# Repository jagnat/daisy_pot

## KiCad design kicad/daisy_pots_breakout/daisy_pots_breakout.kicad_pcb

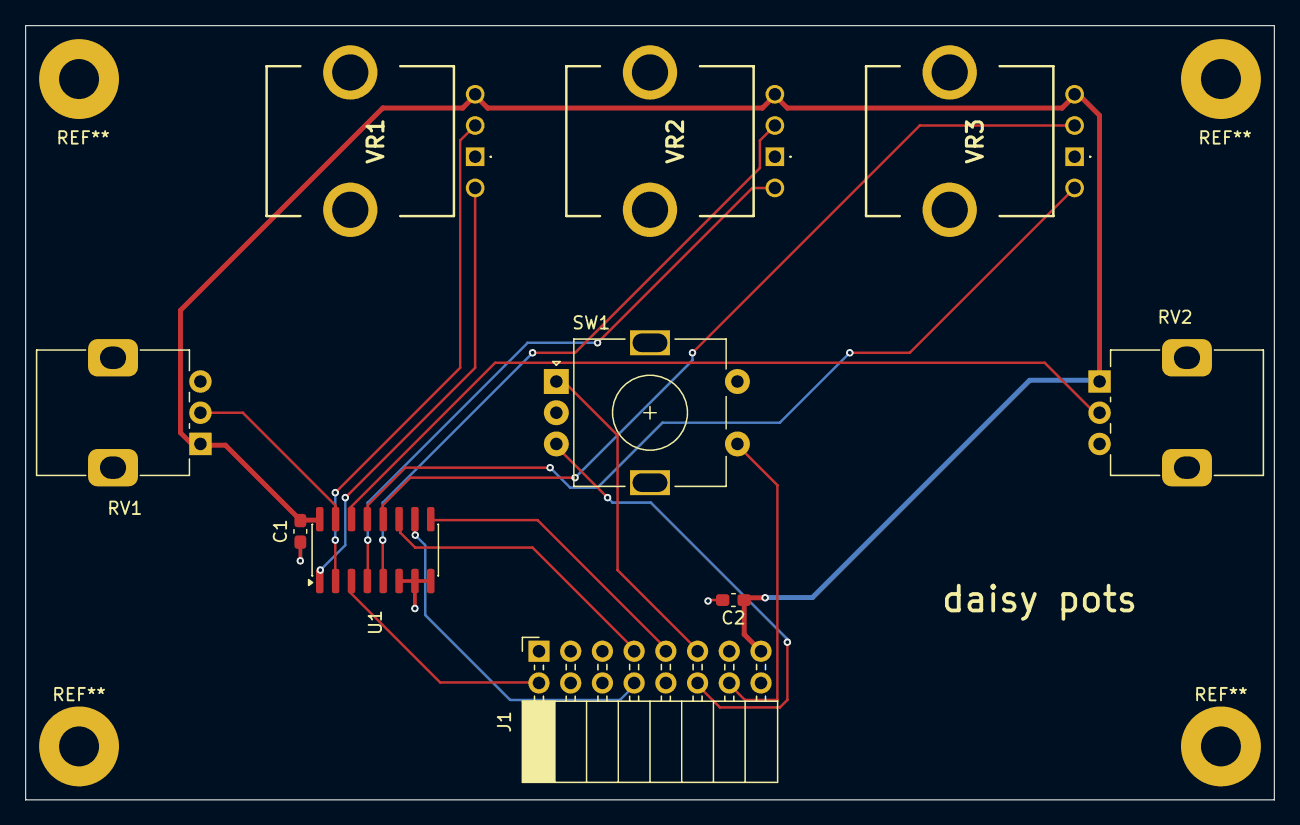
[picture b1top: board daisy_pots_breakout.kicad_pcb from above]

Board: 2 copper layers, 100.0 x 62.0 mm, 10 parts (0 on the bottom side), 17 nets.

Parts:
C1: 100nF; C_0603_1608Metric_Pad1.08x0.95mm_HandSolder
C2: 10uF; C_0603_1608Metric_Pad1.08x0.95mm_HandSolder
J1: Petal_2x08; PinSocket_2x08_P2.54mm_Horizontal
RV1, RV2: 10k; Potentiometer_Alps_RK09K_Single_Vertical
SW1: EC11E; RotaryEncoder_Alps_EC11E-Switch_Vertical_H20mm
U1: 74HC4051D; SOIC-16_3.9x9.9mm_P1.27mm
VR1, VR2, VR3: RV112FF-40B1; RV112FF40B115F0B20K0068

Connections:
+3.3VA: C1.1, C2.1, J1.15, RV1.1, RV2.1, U1.16, VR1.3 (CW), VR2.3 (CW), VR3.3 (CW)
/ADC: J1.2, U1.3
/A_S0: J1.7, U1.11
/A_S1: J1.8, U1.10
/A_S2: J1.9, U1.9
/ENC_A: J1.11, SW1.A
/ENC_B: J1.12, SW1.B
/ENC_SW: J1.14, SW1.S1
/JOY1_X: U1.2, VR1.2 (WIPER1)
/JOY1_Y: U1.1, VR1.A2 (WIPER2)
/JOY2_X: U1.5, VR2.2 (WIPER1)
/JOY2_Y: U1.4, VR2.A2 (WIPER2)
/JOY3_X: U1.12, VR3.2 (WIPER1)
/JOY3_Y: U1.13, VR3.A2 (WIPER2)
/POT1: RV1.2, U1.15
/POT2: RV2.2, U1.14
GND: C1.2, C2.2, J1.1, J1.3, J1.13, J1.16, RV1.3, RV2.3, SW1.C, SW1.S2, U1.6, U1.7, U1.8, VR1.1 (CCW), VR2.1 (CCW), VR3.1 (CCW)

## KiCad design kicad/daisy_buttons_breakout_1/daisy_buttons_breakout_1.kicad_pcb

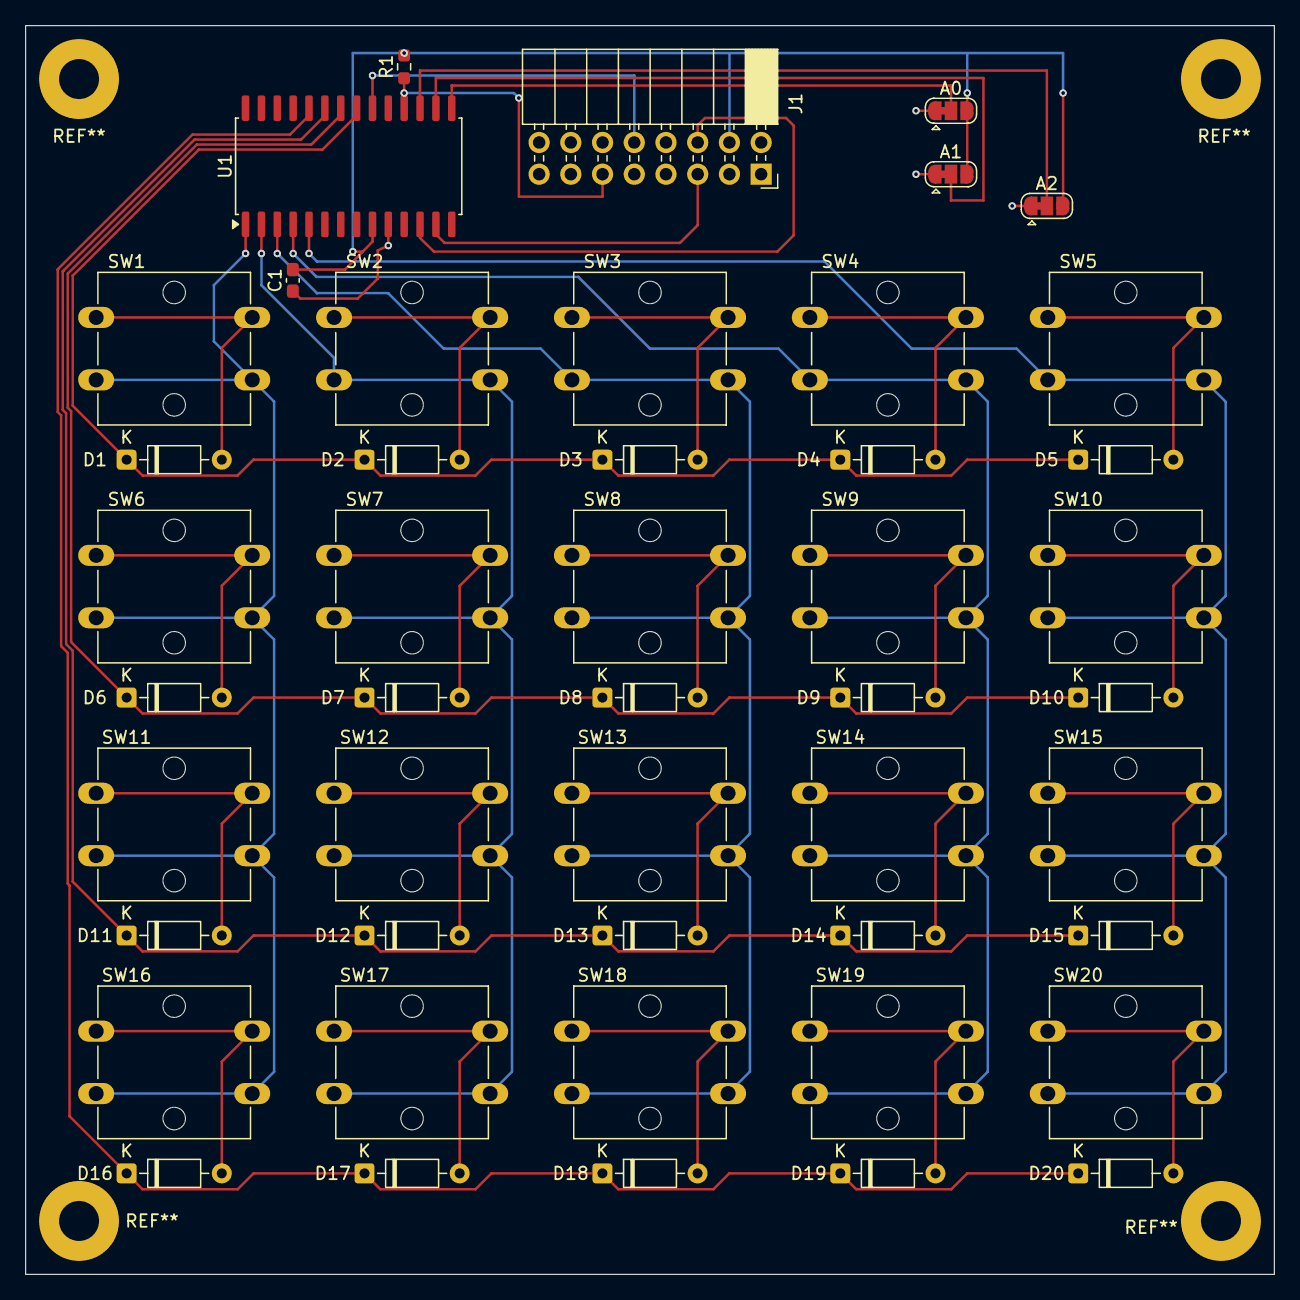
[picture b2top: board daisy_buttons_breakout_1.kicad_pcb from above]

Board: 2 copper layers, 100.0 x 100.0 mm, 47 parts (0 on the bottom side), 38 nets.

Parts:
A0, A1, A2: SolderJumper_3_Bridged12; SolderJumper-3_P1.3mm_Bridged12_RoundedPad1.0x1.5mm
C1: 100nF; C_0603_1608Metric_Pad1.08x0.95mm_HandSolder
D1, D2, D3, D4, D5, D6, D7, D8, D9, D10, D11, D12, D13, D14, D15, D16, D17, D18, D19, D20: D; D_DO-35_SOD27_P7.62mm_Horizontal
J1: Conn_02x08_Odd_Even; PinSocket_2x08_P2.54mm_Horizontal
R1: 10k; R_0603_1608Metric_Pad0.98x0.95mm_HandSolder
SW1, SW2, SW3, SW4, SW5, SW6, SW7, SW8, SW9, SW10, SW11, SW12, SW13, SW14, SW15, SW16, SW17, SW18, SW19, SW20: SW_Push; SW_SPST_Omron_B3F-50xx
U1: MCP23017x-x-SO; SOIC-28W_7.5x17.9mm_P1.27mm

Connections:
/A0: D1.1 (K), D2.1 (K), D3.1 (K), D4.1 (K), D5.1 (K), U1.21 (GPA0)
/A1: D6.1 (K), D7.1 (K), D8.1 (K), D9.1 (K), D10.1 (K), U1.22 (GPA1)
/A2: D11.1 (K), D12.1 (K), D13.1 (K), D14.1 (K), D15.1 (K), U1.23 (GPA2)
/A3: D16.1 (K), D17.1 (K), D18.1 (K), D19.1 (K), D20.1 (K), U1.24 (GPA3)
/B0: SW1.2, SW6.2, SW11.2, SW16.2, U1.1 (GPB0)
/B1: SW2.2, SW7.2, SW12.2, SW17.2, U1.2 (GPB1)
/B2: SW3.2, SW8.2, SW13.2, SW18.2, U1.3 (GPB2)
/B3: SW4.2, SW9.2, SW14.2, SW19.2, U1.4 (GPB3)
/B4: SW5.2, SW10.2, SW15.2, SW20.2, U1.5 (GPB4)
/INT_A: J1.10, U1.20 (INTA)
/RST: J1.11, R1.1, U1.18 (~RESET)
/SCK: J1.6, U1.12 (SCK)
/SDA: J1.5, U1.13 (SDA)
GND: A0.1 (A), A1.1 (A), A2.1 (A), C1.1, J1.1, J1.3, J1.13, J1.16, U1.10 (V_{SS})
unnamed: A0.2 (C), U1.15 (A0)
unnamed: A1.2 (C), U1.16 (A1)
unnamed: A2.2 (C), U1.17 (A2)
unnamed: D1.2 (A), SW1.1
unnamed: D2.2 (A), SW2.1
unnamed: D3.2 (A), SW3.1
unnamed: D4.2 (A), SW4.1
unnamed: D5.2 (A), SW5.1
unnamed: D6.2 (A), SW6.1
unnamed: D7.2 (A), SW7.1
unnamed: D8.2 (A), SW8.1
unnamed: D9.2 (A), SW9.1
unnamed: D10.2 (A), SW10.1
unnamed: D11.2 (A), SW11.1
unnamed: D12.2 (A), SW12.1
unnamed: D13.2 (A), SW13.1
unnamed: D14.2 (A), SW14.1
unnamed: D15.2 (A), SW15.1
unnamed: D16.2 (A), SW16.1
unnamed: D17.2 (A), SW17.1
unnamed: D18.2 (A), SW18.1
unnamed: D19.2 (A), SW19.1
unnamed: D20.2 (A), SW20.1
VCC: A0.3 (B), A1.3 (B), A2.3 (B), C1.2, J1.4, R1.2, U1.9 (V_{DD})

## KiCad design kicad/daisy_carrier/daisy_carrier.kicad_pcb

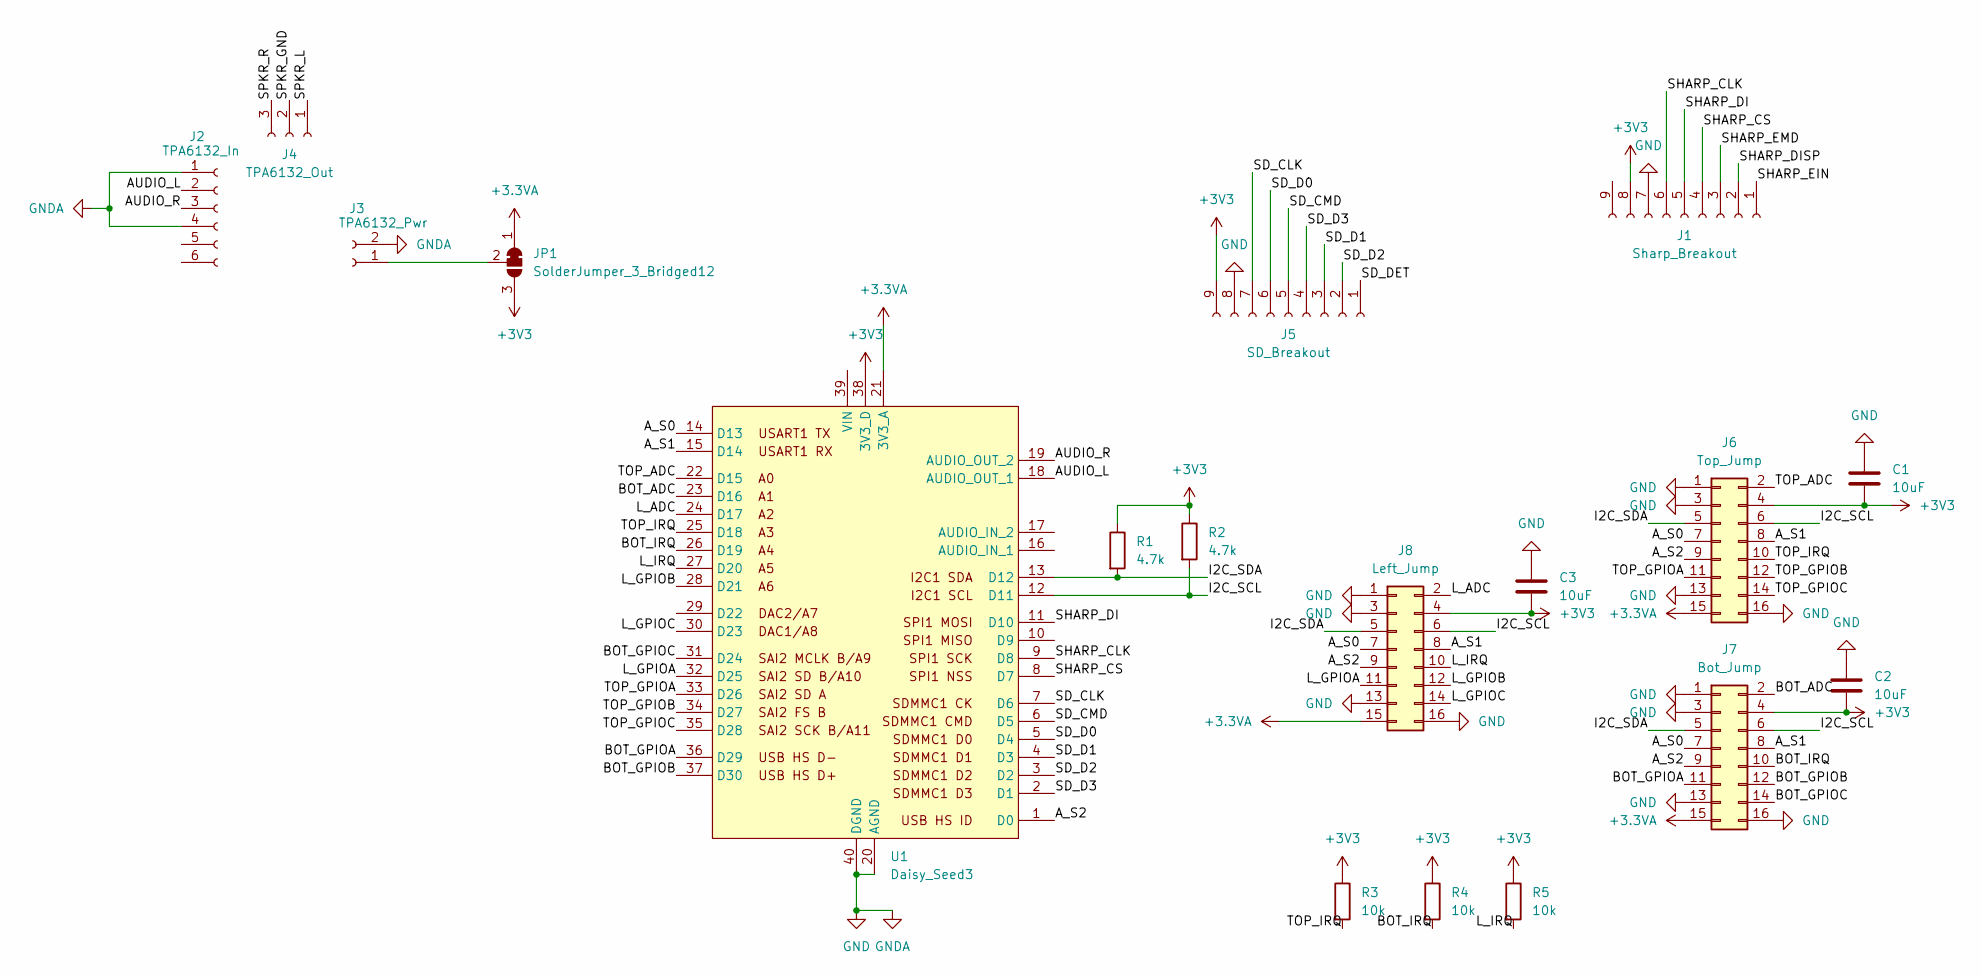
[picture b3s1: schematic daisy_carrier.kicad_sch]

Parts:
C1, C2, C3: 10uF; C_0603_1608Metric_Pad1.08x0.95mm_HandSolder
J1: Sharp_Breakout; PinSocket_1x09_P2.54mm_Vertical
J2: TPA6132_In; PinSocket_1x06_P2.54mm_Vertical
J3: TPA6132_Pwr; PinSocket_1x02_P2.54mm_Vertical
J4: TPA6132_Out; PinSocket_1x03_P2.54mm_Vertical
J5: SD_Breakout; PinSocket_1x09_P2.54mm_Vertical
J6: Top_Jump; PinHeader_2x08_P2.54mm_Horizontal
J7: Bot_Jump; PinHeader_2x08_P2.54mm_Horizontal
J8: Left_Jump; PinHeader_2x08_P2.54mm_Horizontal
JP1: SolderJumper_3_Bridged12; SolderJumper-3_P1.3mm_Bridged12_Pad1.0x1.5mm_NumberLabels
R1, R2: 4.7k; R_0603_1608Metric_Pad0.98x0.95mm_HandSolder
R3, R4, R5: 10k; R_0603_1608Metric_Pad0.98x0.95mm_HandSolder
U1: Daisy_Seed3; DAISY_SEED

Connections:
+3.3VA: J6.15, J7.15, J8.15, JP1.1 (A), U1.21 (3V3_A)
+3V3: C1.2, C2.2, C3.2, J1.8, J5.9, J6.4, J7.4, J8.4, JP1.3 (B), R1.1, R2.1, R3.1, R4.1, R5.1, U1.38 (3V3_D)
/AUDIO_L: J2.2, U1.18 (AUDIO_OUT_1)
/AUDIO_R: J2.3, U1.19 (AUDIO_OUT_2)
/A_S0: J6.7, J7.7, J8.7, U1.14 (D13)
/A_S1: J6.8, J7.8, J8.8, U1.15 (D14)
/A_S2: J6.9, J7.9, J8.9, U1.1 (D0)
/BOT_ADC: J7.2, U1.23 (D16)
/BOT_GPIOA: J7.11, U1.36 (D29)
/BOT_GPIOB: J7.12, U1.37 (D30)
/BOT_GPIOC: J7.14, U1.31 (D24)
/BOT_IRQ: J7.10, R4.2, U1.26 (D19)
/I2C_SCL: J6.6, J7.6, J8.6, R2.2, U1.12 (D11)
/I2C_SDA: J6.5, J7.5, J8.5, R1.2, U1.13 (D12)
/L_ADC: J8.2, U1.24 (D17)
/L_GPIOA: J8.11, U1.32 (D25)
/L_GPIOB: J8.12, U1.28 (D21)
/L_GPIOC: J8.14, U1.30 (D23)
/L_IRQ: J8.10, R5.2, U1.27 (D20)
/SD_CLK: J5.7, U1.7 (D6)
/SD_CMD: J5.5, U1.6 (D5)
/SD_D0: J5.6, U1.5 (D4)
/SD_D1: J5.3, U1.4 (D3)
/SD_D2: J5.2, U1.3 (D2)
/SD_D3: J5.4, U1.2 (D1)
/SD_DET: J5.1
/SHARP_CLK: J1.6, U1.9 (D8)
/SHARP_CS: J1.4, U1.8 (D7)
/SHARP_DI: J1.5, U1.11 (D10)
/SHARP_DISP: J1.2
/SHARP_EIN: J1.1
/SHARP_EMD: J1.3
/SPKR_GND: J4.2
/SPKR_L: J4.1
/SPKR_R: J4.3
/TOP_ADC: J6.2, U1.22 (D15)
/TOP_GPIOA: J6.11, U1.33 (D26)
/TOP_GPIOB: J6.12, U1.34 (D27)
/TOP_GPIOC: J6.14, U1.35 (D28)
/TOP_IRQ: J6.10, R3.2, U1.25 (D18)
GND: C1.1, C2.1, C3.1, J1.7, J2.1, J2.4, J3.2, J5.8, J6.1, J6.3, J6.13, J6.16, J7.1, J7.3, J7.13, J7.16, J8.1, J8.3, J8.13, J8.16, U1.20 (AGND), U1.40 (DGND)
unnamed: J3.1, JP1.2 (C)

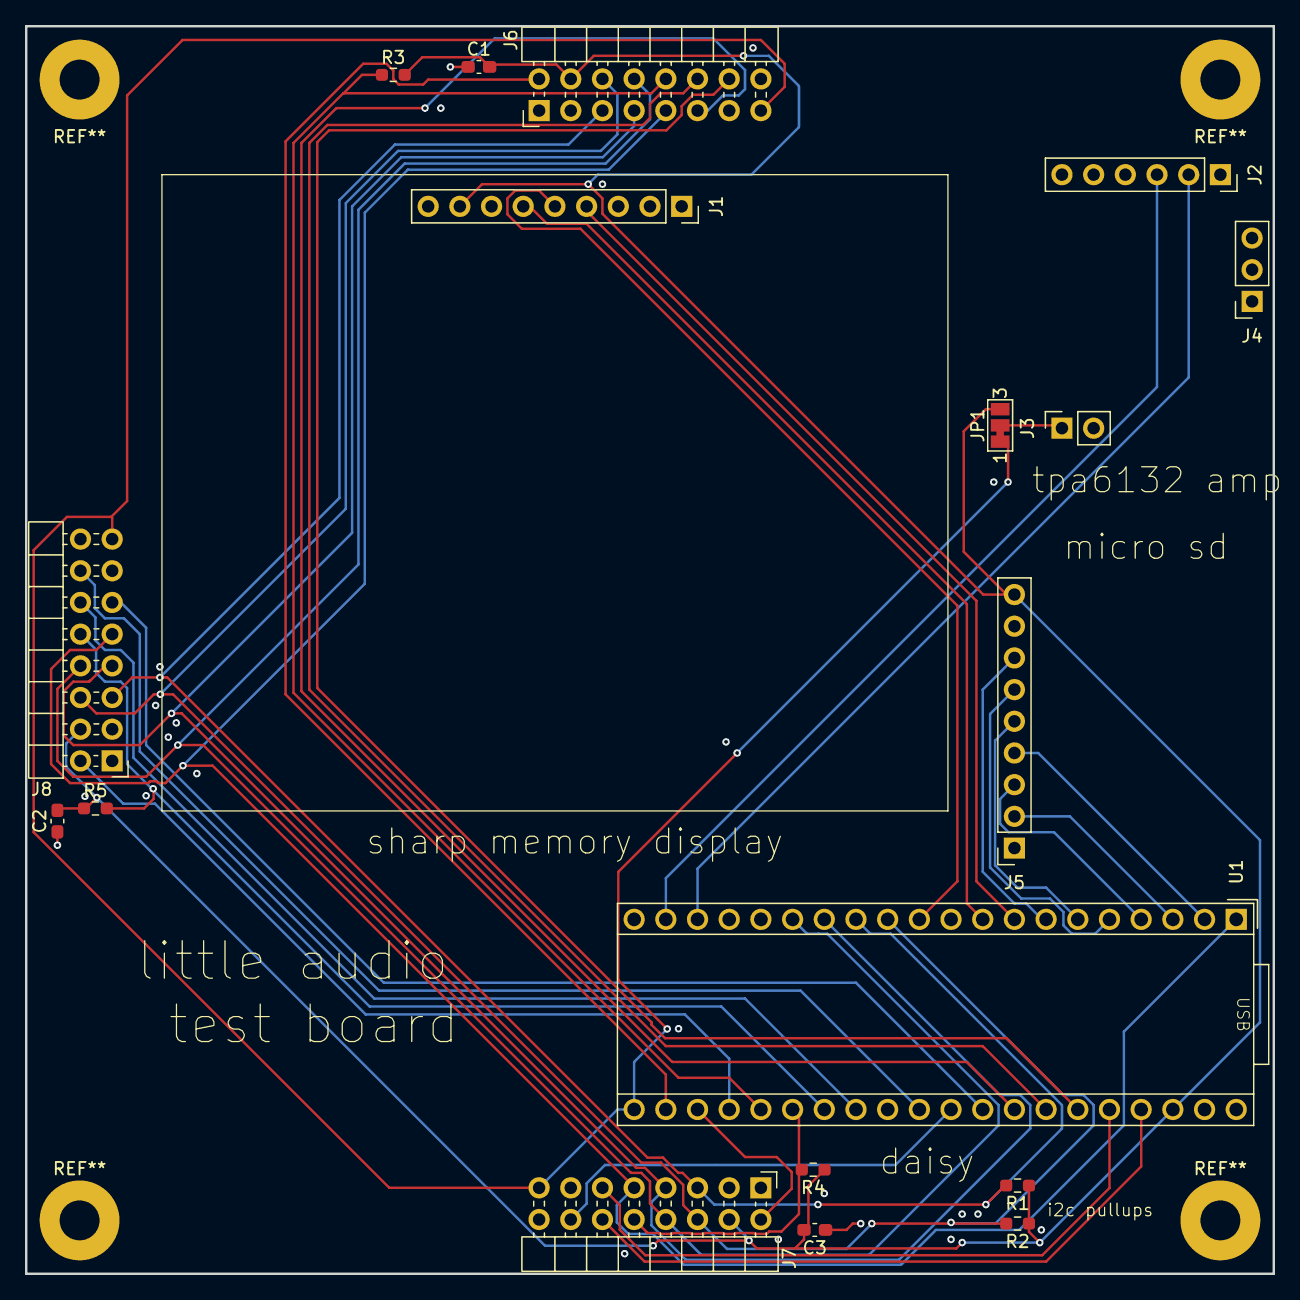
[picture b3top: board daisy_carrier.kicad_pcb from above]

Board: 4 copper layers, 100.0 x 100.0 mm, 18 parts (0 on the bottom side), 35 nets.

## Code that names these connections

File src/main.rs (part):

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        averaging: Some(adc::Averaging::Samples4),
    });

    let mut sharp_cs = gpio::Flex::new(p.PG10);
    sharp_cs.set_as_af_unchecked(5, gpio::AfType::output(gpio::OutputType::PushPull, gpio::Speed::High));
    let mut sharp_cfg = spi::Config::default();
    sharp_cfg.frequency = time::mhz(12);
    sharp_cfg.bit_order = spi::BitOrder::LsbFirst;
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#[embassy_executor::task]
async fn input_task(
    mut adc: Adc<'static, peripherals::ADC1>,
    mut pot1: Peri<'static, peripherals::PC0>,
    mut pot2: Peri<'static, peripherals::PA3>,
    mut volpot: Peri<'static, peripherals::PB1>,
    btn: Peri<'static, peripherals::PB14>) {
    let mut ticker = Ticker::every(Duration::from_millis(10));
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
